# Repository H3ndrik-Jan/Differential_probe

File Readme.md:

# Battery powered differential oscilloscope probe
This repository contains schematics and design files, simulations and measurement results of the probe.
More details: https://hackaday.io/project/181410-battery-powered-differential-probe
# Pictures

# 1Hz-950KHz transfer + THD:

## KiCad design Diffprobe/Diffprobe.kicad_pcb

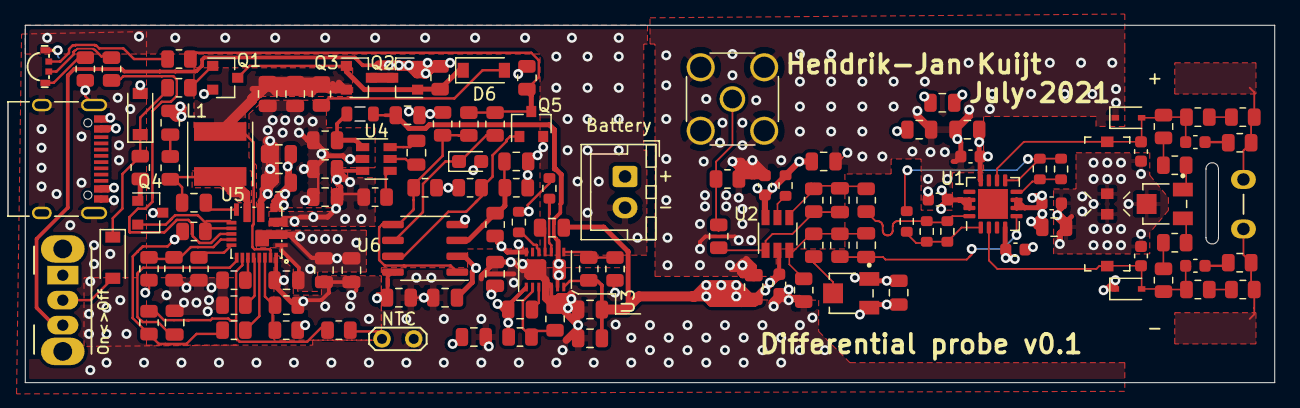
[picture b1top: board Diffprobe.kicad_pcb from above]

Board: 4 copper layers, 100.0 x 28.6 mm, 130 parts (0 on the bottom side), 70 nets.

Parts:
BT1: Battery; JST_XH_B2B-XH-A_1x02_P2.50mm_Vertical
C1, C2, C7, C22: 100n; C_0603_1608Metric
C3, C4: 3p; C_0603_1608Metric
C5, C6, C11, C15, C16, C17, C18, C19, C20, C25, C28, C29, C30, C32: 10u; C_0805_2012Metric
C8, C12, C13, C14, C21, C42, C43, C44: 100n; C_0805_2012Metric
C9, C10, C31: DNP; C_0805_2012Metric
C23, C24: 1n; C_0603_1608Metric
C26, C27: 10n; C_0805_2012Metric
C33, C34: 1u; C_0805_2012Metric
C35: TBD; C_0805_2012Metric
C36, C39, C40: 3.3u; C_0805_2012Metric
C37, C38: DNP; R_0603_1608Metric
C41: 10u; CP_EIA-2012-15_AVX-P
C45, C46: DNP; C_0603_1608Metric
CV3, CV4: 30p; C_Trimmer_Murata_TZC3
D1, D2: ESD128; D_SOD-323
D3: LED_ABGR; MHS110_RGB
D4, D5, D6: 1N4148W; D_SOD-123
FB1: Ferrite_Bead; L_0805_2012Metric
J1: Conn_Coaxial; SMA_Wurth_60312002114503_Vertical
J2: Conn_01x02_Female; probepads
L1: 8.2uH; L_Taiyo-Yuden_MD-5050
P1: USB_C_Plug_USB2.0; USB_C_Receptacle_XKB_U262-16XN-4BVC11
Q1, Q5: MMBT3904; SOT-23
Q2, Q3, Q4: DMG3415; SOT-23
R1, R3: 330R; R_0603_1608Metric
R2: DNP; R_0603_1608Metric
R4, R5, R6, R7: 330R; R_0805_2012Metric
R8: 50R; R_0805_2012Metric
R9: 1Meg; R_0805_2012Metric
R10, R11, R52, R53: 2Meg; R_0805_2012Metric
R12, R13: 402K; R_0805_2012Metric
R14, R15: 1K tf; R_0805_2012Metric
R16, R18, R27, R42: 22K; R_0805_2012Metric
R17, R41, R43: 100K; R_0805_2012Metric
R19, R21, R44: 33K; R_0805_2012Metric
R20: 12K; R_0805_2012Metric
R22: 2K; R_0805_2012Metric
R23, R37: 1K; R_0805_2012Metric
R24, R38: DNP; R_0805_2012Metric
R25: 3,3K; R_0805_2012Metric
R26: 220K; R_0805_2012Metric
R28: 4.42K; R_0805_2012Metric
R29: 36K; R_0805_2012Metric
R30, R39, R49: 10K; R_0805_2012Metric
R31, R32, R40: 10K; R_0603_1608Metric
R33, R35: 11K; R_0805_2012Metric
R34, R36: 3.57K; R_0805_2012Metric
R45, R47, R48, R50, R51: 47K; R_0805_2012Metric
R46: 27K; R_0805_2012Metric
R54, R55: 42.2K; R_0805_2012Metric
RV1: 20K; TRIM_3313J-1-103E
RV2: 500R; TRIM_3313J-1-103E
SW1: SW_SPDT; SW_CuK_OS102011MA1QN1_SPDT_Angled
TH1: Thermistor_NTC; TestPoint_2Pads_Pitch2.54mm_Drill0.8mm
U1: ADA4817-2; LFCSP-16-1EP_4x4mm_P0.65mm_EP2.4x2.4mm
U2: LTC6228xS6; TSOT-23-6
U3: LT3032; Linear_DE14MA
U4: LM2776; SOT-23-6
U5: SY6926; QFN-20_L4.0-W4.0-P0.45-BL
U6: TS372; SO-8_3.9x4.9mm_P1.27mm

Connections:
+5V: C1.1, C5.1, C7.1, C17.1, C21.1, C23.1, C26.1, C28.1, C39.1, C40.1, R31.2, R33.1, RV1.3, U1.6, U1.7, U1.14, U1.15, U2.6, U3.1
-5V: C2.2, C6.2, C8.2, C18.2, C22.2, C24.2, C27.1, C29.1, C39.2, C40.2, R35.1, RV1.1, U1.4, U1.12, U2.2, U3.7
-VDC: C36.1, FB1.1, U3.6, U3.9
/Battery management/BUS: C15.1, C19.1, D3.1, R24.2, R27.1, R43.1, U5.4
/Battery management/Enable: Q4.2, R43.2, U5.8, U5.9
/Battery management/VUSB: C11.1, C12.1, C25.1, D5.2, P1.A4, P1.A9, P1.B4, P1.B9, R19.1, U5.1, U5.2
/IN+: J2.2, R15.2, R53.2
/IN-: J2.1, R14.2, R52.2
/OUTPUT: J1.1, R8.1, R9.1
Bat_Indicator: Q5.3, R23.2, R48.1, R49.1, R51.2
Battery: BT1.1, C43.1, Q2.2, R41.1, SW1.3, U6.2
GND: BT1.2, C1.2, C2.1, C5.2, C6.1, C7.2, C8.1, C11.2, C12.2, C13.2, C15.2, C16.2, C17.2, C18.1, C19.2, C20.2, C21.2, C22.1, C23.2, C24.1, C25.2, C28.2, C29.2, C30.2, C31.1, C32.2, C34.2, C35.2, C36.2, C41.2, C42.2, C43.2, C44.2, C45.2, C46.1, CV3.1, CV4.1, D1.1, D2.1, J1.2, P1.A1, P1.A12, P1.B1, P1.B12, P1.S1, Q1.2, Q4.3, Q5.2, R6.2, R9.2, R20.2, R21.2, R22.2, R25.2, R26.1, R30.2, R34.2, R36.2, R45.2, R47.2, RV2.2, TH1.2, U3.4, U3.5, U4.2, U5.5, U5.20, U6.4
unnamed: C3.1, C45.1, CV3.2, D1.2, R10.1, R12.1, U1.2
unnamed: C3.2, R14.1
unnamed: C4.1, C46.2, CV4.2, D2.2, R11.1, R13.2, U1.10
unnamed: C4.2, R15.1
unnamed: C9.1, R5.1, R6.1, R18.2, U2.3
unnamed: C10.1, R7.1, R8.2, U2.1
unnamed: C10.2, R4.1, R7.2, U2.4
unnamed: C13.1, U5.13
unnamed: C14.1, L1.2, R38.2, U5.6
unnamed: C14.2, U5.7
unnamed: C20.1, C30.1, L1.1, Q3.2, R17.1, U5.19
unnamed: C26.2, U3.3
unnamed: C27.2, U3.11
unnamed: C31.2, R38.1
unnamed: C33.1, U4.5
unnamed: C33.2, U4.6
unnamed: C34.1, FB1.2, U4.1
unnamed: C37.1, R1.1, R4.2, U1.13, U1.16
unnamed: C37.2, R1.2, R2.1, U1.1
unnamed: C38.1, R2.2, R3.1, U1.9
unnamed: C9.2, C38.2, R3.2, R5.2, U1.5, U1.8
unnamed: C41.1, R48.2, U6.6
unnamed: C42.1, R44.2, R45.1, U6.3
unnamed: D3.2, R23.1
unnamed: D3.3, R37.1
unnamed: D3.4, R22.1
unnamed: D4.1, D5.1, R16.2, R42.2
unnamed: D4.2, SW1.2
unnamed: D6.1, Q1.3, Q2.1, Q3.1, R41.2
unnamed: D6.2, R17.2
unnamed: Q1.1, R16.1
unnamed: Q2.3, Q3.3
unnamed: Q4.1, R42.1
unnamed: Q5.1, R50.2, U6.7
unnamed: R10.2, R52.1
unnamed: R11.2, R53.1
unnamed: R12.2, R54.1
unnamed: R13.1, R55.2
unnamed: R18.1, RV1.2
unnamed: R19.2, R20.1, U5.11
unnamed: R21.1, U5.15
unnamed: R24.1, U5.17
unnamed: R25.1, U5.12
unnamed: R26.2, U5.16
unnamed: R27.2, R28.1, U5.14
unnamed: R28.2, TH1.1
unnamed: R29.2, R30.1, U5.18
unnamed: R31.1, U2.5
unnamed: R32.2, U3.12
unnamed: R33.2, R34.1, U3.2
unnamed: R35.2, R36.1, U3.8
unnamed: R37.2, U5.10
unnamed: R39.2, U4.4
unnamed: R40.2, U3.10
unnamed: R46.2, R47.1, R49.2, U6.1, U6.5
unnamed: R54.2, RV2.3
unnamed: R55.1, RV2.1
VDC: C16.1, C32.1, C35.1, C44.1, R29.1, R32.1, R39.1, R40.1, R44.1, R46.1, R50.1, R51.1, U3.14, U4.3, U5.3, U6.8

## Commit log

2021-07-13 two symbols added
2021-07-15 differential amplifier + simulations + batterycharger added
2021-07-24 more circuitry & simulation added
2021-08-22 gitignore added
2021-10-05 readme, 3d files, measurements and more added
